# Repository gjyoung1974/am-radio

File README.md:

# AM Broadcast Receiver: 6-transistor superhet KiCad

## What it is

A classic 1960's style 455 kHz superheterodyne AM receiver, 4.5 V (3×AAA), negative ground, six 2N3904 NPN transistors:

| Stage | Parts |
|---|---|
| Antenna / tuning | L1 ferrite loopstick, VC1 2-gang polyvaricon (Variable Capacitor) (140 pF antenna gang, 60 pF oscillator gang, trimmers built in) |
| Converter (mixer + local oscillator) | Q1, L2 oscillator coil (i.e. Xicon 42IF110, red), C1 emitter injection, R1/R2/R3 bias |
| IF amp 1 with AGC | T1 (42IF101 yellow) => Q2 => T2; R4/R5/C3 form the AGC network |
| IF amp 2 | T2 (42IF102 white) => Q3 => T3 |
| Detector / volume | T3 (42IF103 black) => D1 1N34A germanium diode => C7 => RV1 10k log |
| Audio driver | C8 => Q4 => T4 (Xicon 42TU013, 1k CT : 8 CT) |
| Class-B push-pull output | Q5/Q6 => T5 (Xicon 42TU200, 200 CT : 8) => J1 speaker terminals; R14/R15 set base bias |
| Power | BT1 3×AAA (Keystone 2479 board-mount holder), SW1 slide switch, C12; R16/C13 make the decoupled `V_RF` rail for the RF/IF stages 
|Detected audio is negative-side, so AGC lowers Q2's base bias on strong stations.

## Files

- `am-radio.kicad_sch` / `am-radio.kicad_pcb` / `am-radio.kicad_pro` — the project.
- `audio.kicad_sym` — custom symbols: Xicon 42IF10x IF transformer, 42IF110 oscillator coil, 42TU013 / 42TU200 audio transformers (6-pin, pin numbers match the footprint pads), 2-gang polyvaricon, ferrite rod coil, `V_RF` power symbol. Your original `IF_Transformer_AM` symbol is kept for reference.
- `audio.pretty/` — footprints: `Xicon_42IF10x` (0.4" can, 3+3 pins on 0.135" pitch, rows 0.27" apart, from Xicon datasheet XC-600131), `Polyvaricon_CBM-223P_Wired`, `Ferrite_Rod_Antenna_Coil`, plus your `Xicon_42TU200-RC` (courtyard moved from the invalid "Rescue" layer to F.CrtYd).
- `am-radio-outputs/` — schematic PDF, grouped BOM (CSV), PCB layer PDF, top/bottom renders, gerbers + Excellon drill files.
- `am-radio-backups/original-sketch/` — your original schematic and symbol library before this rework (also in the dated backup zips).
- `tools/` — the Python generators used to build the schematic (`gen_sch.py`), libraries (`gen_libs.py`), board (`build_pcb.py`) and ground pour / labels (`finish_pcb.py`). Run with the system `python3` (it has KiCad's `pcbnew` module).

## Board

110 × 83 × 1.6 mm, 2 layers, sized to the 3D-printed case in `case/case.FCStd` (rev 1.1; the 180 × 62 mm rev 1.0 board is kept in `am-radio-backups/rev1.0-180x62/`).

Case fit (all taken from the FreeCAD model):

| Item | Value |
|---|---|
| Case | 115 × 88 × 35 mm, 2 mm walls, open top; cavity 111 × 84 mm |
| Board | 110 × 83 mm, 0.5 mm clearance per side |
| Standoffs | 4, Ø6 mm, 18 mm tall on the 2 mm base; board top face at 21.6 mm |
| Mounting holes | 2.7 mm (M2.5 self-tapping into the 2.5 mm standoff holes), centres 2.3 mm in from each edge = 105.4 × 78.4 mm pattern; 6.4 mm copper-free keepouts on both sides |
| Speaker | 76 mm square, 16 mm deep, centred under the board (board x 4.5–80.5, y 3.5–79.5); only 2 mm between it and the back of the board, so nothing is mounted on the back |
| Speaker leads | 3.5 mm pass-through hole at board (107.3, 67.5) next to J1, in the 29 mm strip east of the speaker where there is 18 mm under the board |
| Height above board | 13.4 mm to the top of the case: fine for the 10 mm IF cans and TO-92s; **check** the Keystone 2479 holder (≈13 mm), the 42TU audio transformers, and plan lid holes for the VC1 and RV1 shafts and a side slot for SW1 (it sits 4 mm from the right wall) |
| Case CornerHole | the 12 × 12 mm hole in the base plate (case X 46–58, Y 20–32) is under board x 88.5–100.5, y 9.5–21.5; only top-side parts (T2, L1, C12) are above it, so nothing on the board depends on it |

Coordinates: board x = case X + 42.5, board y = 41.5 − case Y (board origin top-left, y down, as in KiCad).

Layout: ferrite rod along the top edge with the tuning cap in the top-left corner (terminals facing the rod), 3×AAA holder standing on end along the left edge, RF chain left => right across the middle (L2, Q1, T1, Q2, T2, Q3) with T3 turning down the right edge, detector and volume pot below it, driver T4 on end in the middle, push-pull pair below it, output transformer T5 bottom-right with the speaker terminal block and wire hole beside it, power switch and C12 in the top-right corner. Full GND pour on the back. Tracks 0.6 mm (0.8–1.0 mm for GND / +BATT / V_RF), 0.2 mm clearance, 0.9/0.5 mm vias, 0.5 mm hole-to-hole.

## Things to verify before ordering a PCB

- **VC1 footprint is unverified.** No reliable drawing of the CBM-223P terminal layout exists online, so the footprint is a "wired" one: 20 × 20 mm outline, three solder pads (O, G, A) along the bottom edge for short leads, and two 2.7 mm holes for M2.5 mounting screws on a guessed 15 mm spacing. Measure your part and adjust `gen_libs.py` (or edit the footprint) if you want it to drop straight in.
- **Battery holder height.** The 3×AA holder (60 × 50 × 16 mm) did not fit the case, so BT1 is now a Keystone 2479 3×AAA holder (53.6 × 38.6 mm footprint, about 13 mm tall). Confirm its height against the 13.4 mm left above the board, or use a wired 3×AAA pack fixed to the lid and solder the leads to the BT1 pads.
- **Oscillator phasing.** If the oscillator does not start, swap the L2 pin 4 / pin 6 feedback leads (the 42IF110 datasheet does not give winding order?).

## Alignment

1. Set VC1 fully closed (max capacitance). Adjust the L2 slug so the local oscillator is at about 985 kHz (receives 530 kHz). At the high end use VC1's oscillator trimmer for about 2055 kHz (1600 kHz).
2. Peak T1, T2, T3 slugs for maximum audio on a weak station (they are pre-tuned to 455 kHz and need only a touch).
3. Peak L1 by sliding the coil along the rod at the low end of the band and with VC1's antenna trimmer at the high end.
4. Expected currents: converter ≈ 0.4 mA, IF stages ≈ 0.5 mA each, driver ≈ 1.7 mA, output pair a few mA idle. Total idle ≈ 5–8 mA at 4.5 V.

## Regenerating

```
python3 tools/gen_libs.py                       # symbols + footprints
python3 tools/gen_sch.py                        # schematic
kicad-cli sch export netlist --format kicadsexpr -o am-radio.net am-radio.kicad_sch
python3 tools/build_pcb.py am-radio.net placed.kicad_pcb          # placed, unrouted board (110 x 83, case holes, wire hole)
python3 ~/src/KiCadRoutingTools/route.py placed.kicad_pcb routed.kicad_pcb \
    --track-width 0.6 --clearance 0.2 --via-size 0.9 --via-drill 0.5 \
    --power-nets GND V_RF +BATT --power-nets-widths 0.8 0.8 1.0 \
    --board-edge-clearance 0.5 --hole-to-hole-clearance 0.5
python3 tools/finish_pcb.py routed.kicad_pcb am-radio.kicad_pcb   # GND pour, standoff keepouts, stub cleanup, labels
kicad-cli pcb drc --schematic-parity --severity-all am-radio.kicad_pcb
```

---
2026 - Gordon Young WA8Q

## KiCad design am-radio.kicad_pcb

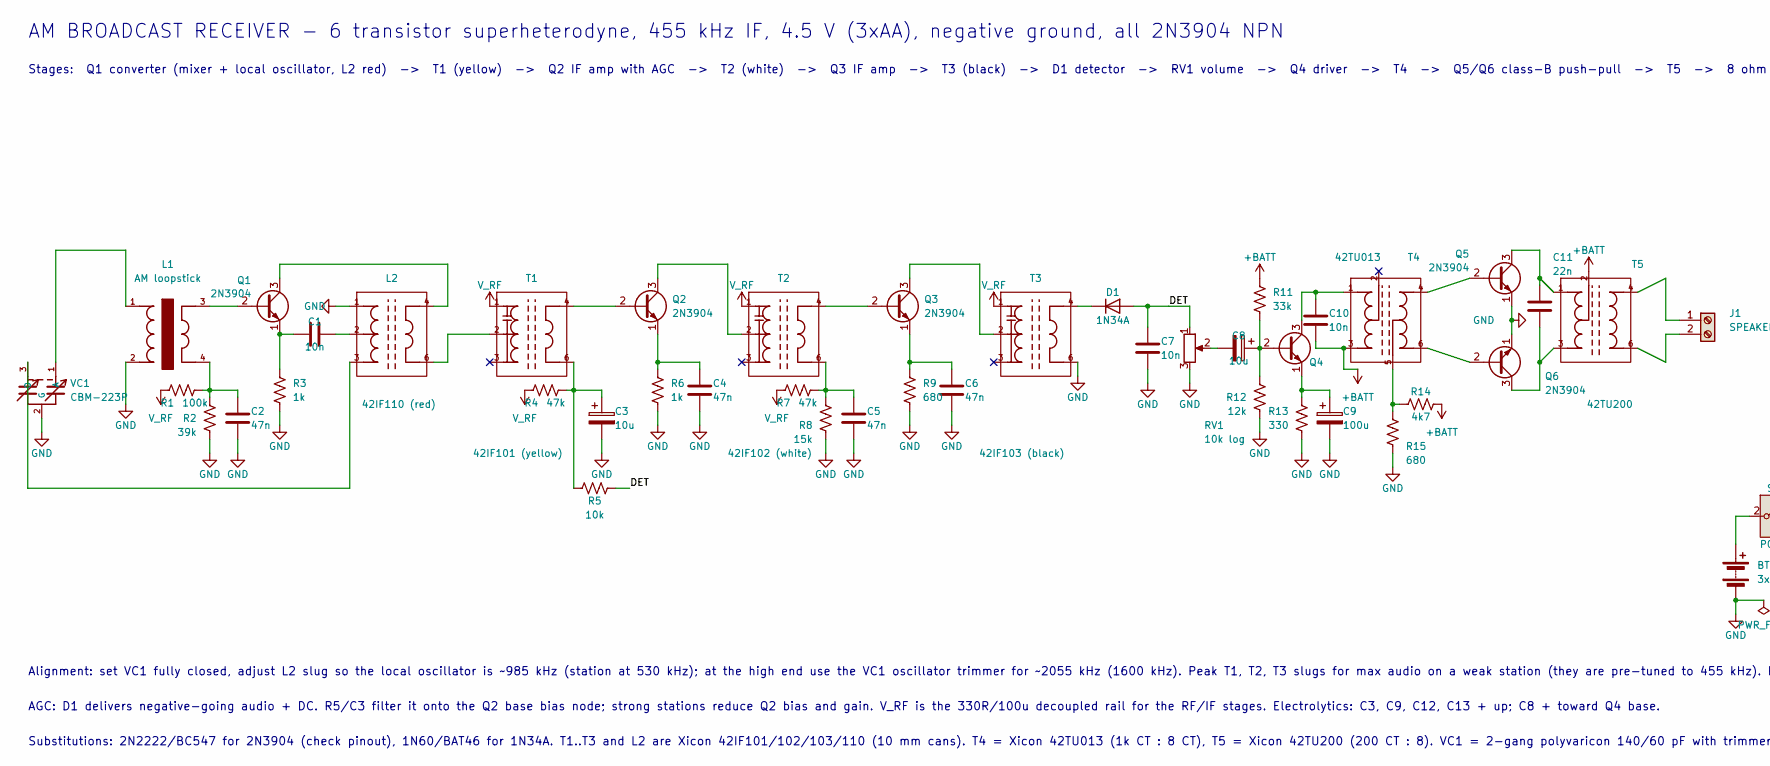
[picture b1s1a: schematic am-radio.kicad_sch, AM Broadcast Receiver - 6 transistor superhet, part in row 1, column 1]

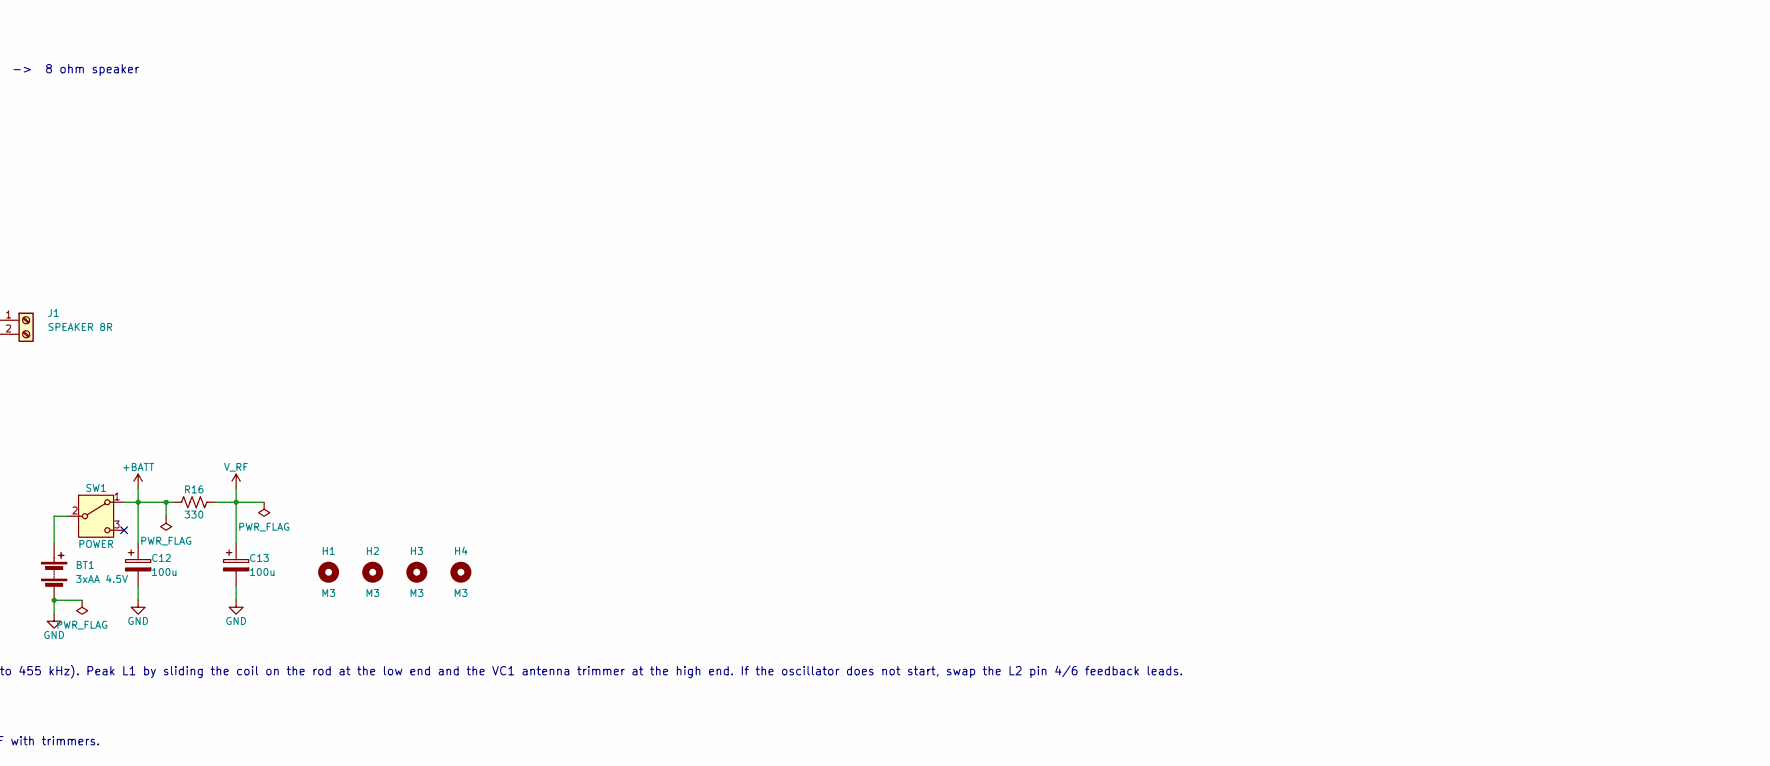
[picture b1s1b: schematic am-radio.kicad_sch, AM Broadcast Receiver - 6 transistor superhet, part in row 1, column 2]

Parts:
BT1: 3xAA 4.5V; BatteryHolder_TruPower_BH-331P_3xAA
C1, C7, C10: 10n; C_Disc_D5.0mm_W2.5mm_P5.00mm
C2, C4, C5, C6: 47n; C_Disc_D5.0mm_W2.5mm_P5.00mm
C3, C8: 10u; CP_Radial_D5.0mm_P2.00mm
C9, C12, C13: 100u; CP_Radial_D5.0mm_P2.00mm
C11: 22n; C_Disc_D5.0mm_W2.5mm_P5.00mm
D1: 1N34A; D_DO-35_SOD27_P10.16mm_Horizontal
H1, H2, H3, H4: M3; MountingHole_3.2mm_M3
J1: SPEAKER 8R; TerminalBlock_Altech_AK300-2_P5.00mm
L1: AM loopstick; Ferrite_Rod_Antenna_Coil
L2: 42IF110 (red); Xicon_42IF10x
Q1, Q2, Q3, Q4, Q5, Q6: 2N3904; TO-92
R1: 100k; R_Axial_DIN0204_L3.6mm_D1.6mm_P5.08mm_Horizontal
R2: 39k; R_Axial_DIN0204_L3.6mm_D1.6mm_P5.08mm_Horizontal
R3, R6: 1k; R_Axial_DIN0204_L3.6mm_D1.6mm_P5.08mm_Horizontal
R4, R7: 47k; R_Axial_DIN0204_L3.6mm_D1.6mm_P5.08mm_Horizontal
R5: 10k; R_Axial_DIN0204_L3.6mm_D1.6mm_P5.08mm_Horizontal
R8: 15k; R_Axial_DIN0204_L3.6mm_D1.6mm_P5.08mm_Horizontal
R9, R15: 680; R_Axial_DIN0204_L3.6mm_D1.6mm_P5.08mm_Horizontal
R11: 33k; R_Axial_DIN0204_L3.6mm_D1.6mm_P5.08mm_Horizontal
R12: 12k; R_Axial_DIN0204_L3.6mm_D1.6mm_P5.08mm_Horizontal
R13, R16: 330; R_Axial_DIN0204_L3.6mm_D1.6mm_P5.08mm_Horizontal
R14: 4k7; R_Axial_DIN0204_L3.6mm_D1.6mm_P5.08mm_Horizontal
RV1: 10k log; Potentiometer_Bourns_PTV09A-1_Single_Vertical
SW1: POWER; SW_Slide_SPDT_Straight_CK_OS102011MS2Q
T1: 42IF101 (yellow); Xicon_42IF10x
T2: 42IF102 (white); Xicon_42IF10x
T3: 42IF103 (black); Xicon_42IF10x
T4: 42TU013; Xicon_42TU200-RC
T5: 42TU200; Xicon_42TU200-RC
VC1: CBM-223P; Polyvaricon_CBM-223P_Wired

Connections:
+BATT: C10.2, C12.1, R11.1, R14.2, R16.1, SW1.1 (A), T4.3, T5.2
/DET: C7.1, D1.2 (A), R5.2, RV1.1
GND: BT1.2 (-), C2.2, C3.2, C4.2, C5.2, C6.2, C7.2, C9.2, C12.2, C13.2, L1.2, L2.1, Q5.1 (E), Q6.1 (E), R2.2, R3.2, R6.2, R8.2, R9.2, R12.2, R13.2, R15.2, RV1.3, T3.6, VC1.2 (G)
unnamed: BT1.1 (+), SW1.2 (B)
unnamed: C1.2, L2.2
unnamed: C2.1, L1.4, R1.2, R2.1
unnamed: C3.1, R4.2, R5.1, T1.6
unnamed: C5.1, R7.2, R8.1, T2.6
unnamed: C8.2, RV1.2
unnamed: D1.1 (K), T3.4
unnamed: J1.1, T5.4
unnamed: J1.2, T5.6
unnamed: L2.6, T1.2
unnamed: L1.3, Q1.2 (B)
unnamed: L2.4, Q1.3 (C)
unnamed: C1.1, Q1.1 (E), R3.1
unnamed: Q2.2 (B), T1.4
unnamed: Q2.3 (C), T2.2
unnamed: C4.1, Q2.1 (E), R6.1
unnamed: Q3.2 (B), T2.4
unnamed: Q3.3 (C), T3.2
unnamed: C6.1, Q3.1 (E), R9.1
unnamed: C8.1, Q4.2 (B), R11.2, R12.1
unnamed: C10.1, Q4.3 (C), T4.1
unnamed: C9.1, Q4.1 (E), R13.1
unnamed: Q5.2 (B), T4.4
unnamed: C11.1, Q5.3 (C), T5.1
unnamed: Q6.2 (B), T4.6
unnamed: C11.2, Q6.3 (C), T5.3
unnamed: R14.1, R15.1, T4.5
unnamed: L1.1, VC1.1 (A)
unnamed: L2.3, VC1.3 (O)
V_RF: C13.1, R1.1, R4.1, R7.1, R16.2, T1.1, T2.1, T3.1

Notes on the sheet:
AM BROADCAST RECEIVER - 6 transistor superheterodyne, 455 kHz IF, 4.5 V (3xAA), negative ground, all 2N3904 NPN
Stages: Q1 converter (mixer + local oscillator, L2 red) -> T1 (yellow) -> Q2 IF amp with AGC -> T2 (white) -> Q3 IF amp -> T3 (black) -> D1 detector -> RV1 volume -> Q4 driver -> T4 -> Q5/Q6 class-B push-pull -> T5 -> 8 ohm speaker
Alignment: set VC1 fully closed, adjust L2 slug so the local oscillator is ~985 kHz (station at 530 kHz); at the high end use the VC1 oscillator trimmer for ~2055 kHz (1600 kHz). Peak T1, T2, T3 slugs for max audio on a weak station (they are pre-tuned to 455 kHz). Peak L1 by sliding the coil on th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
AGC: D1 delivers negative-going audio + DC. R5/C3 filter it onto the Q2 base bias node; strong stations reduce Q2 bias and gain. V_RF is the 330R/100u decoupled rail for the RF/IF stages. Electrolytics: C3, C9, C12, C13 + up; C8 + toward Q4 base.
Substitutions: 2N2222/BC547 for 2N3904 (check pinout), 1N60/BAT46 for 1N34A. T1..T3 and L2 are Xicon 42IF101/102/103/110 (10 mm cans). T4 = Xicon 42TU013 (1k CT : 8 CT), T5 = Xicon 42TU200 (200 CT : 8). VC1 = 2-gang polyvaricon 140/60 pF with trimmers.

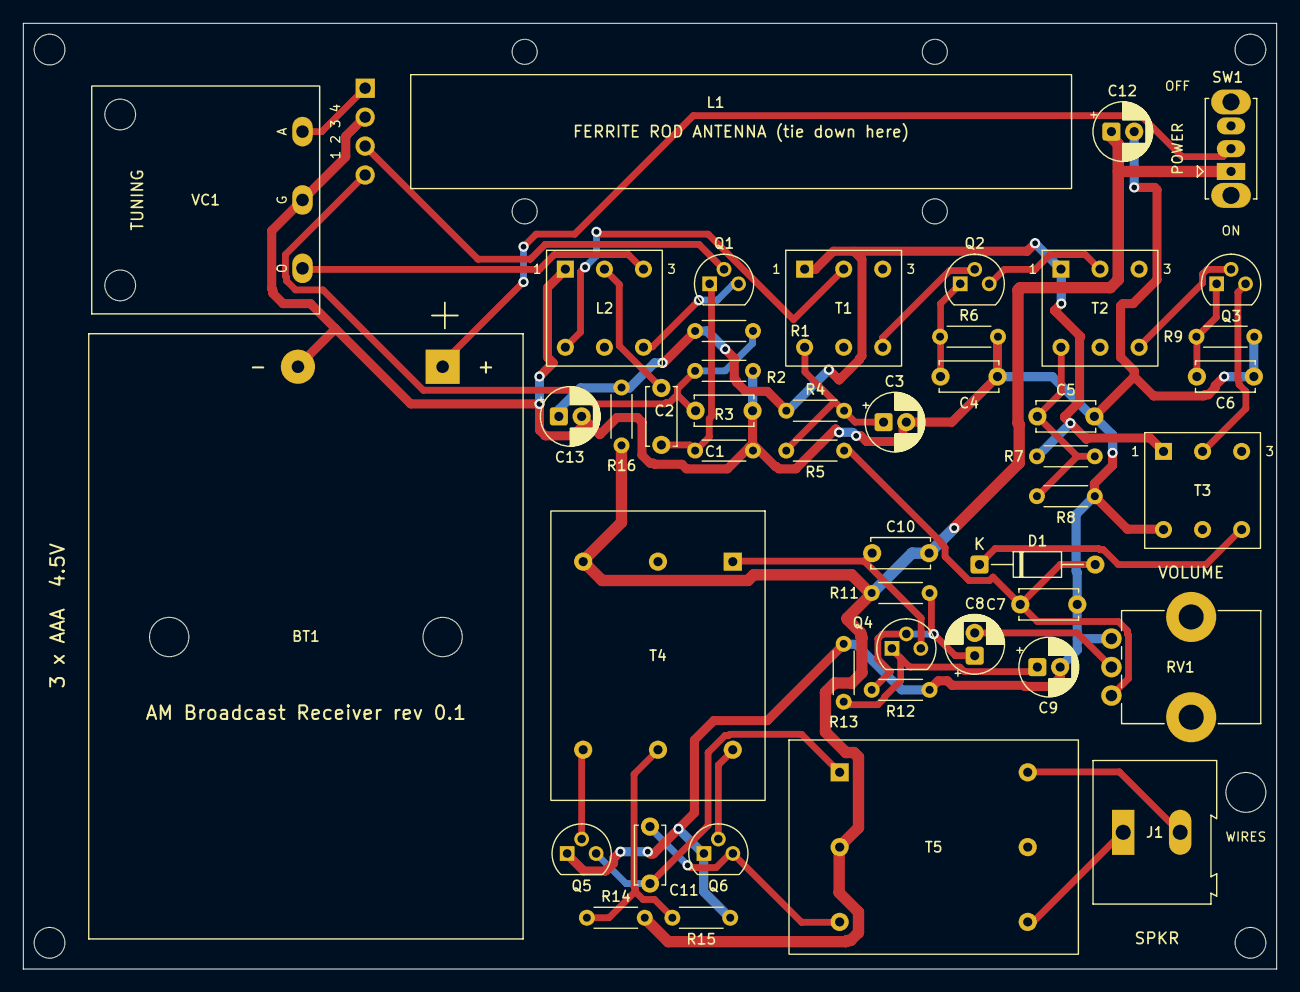
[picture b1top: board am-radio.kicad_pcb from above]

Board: 2 copper layers, 110.0 x 83.0 mm, 51 parts (0 on the bottom side), 33 nets.

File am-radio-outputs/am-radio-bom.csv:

"Ref","Value","Footprint"
"BT1","3xAAA 4.5V","Battery:BatteryHolder_Keystone_2479_3xAAA"
"C1,C7,C10","10n","Capacitor_THT:C_Disc_D5.0mm_W2.5mm_P5.00mm"
"C2,C4-C6","47n","Capacitor_THT:C_Disc_D5.0mm_W2.5mm_P5.00mm"
"C3,C8","10u","Capacitor_THT:CP_Radial_D5.0mm_P2.00mm"
"C9,C12,C13","100u","Capacitor_THT:CP_Radial_D5.0mm_P2.00mm"
"C11","22n","Capacitor_THT:C_Disc_D5.0mm_W2.5mm_P5.00mm"
"D1","1N34A","Diode_THT:D_DO-35_SOD27_P10.16mm_Horizontal"
"H1-H4","M2.5","MountingHole:MountingHole_2.7mm_M2.5"
"J1","SPEAKER 8R","TerminalBlock:TerminalBlock_Altech_AK300-2_P5.00mm"
"L1","AM loopstick","audio:Ferrite_Rod_Antenna_Coil"
"L2","42IF110 (red)","audio:Xicon_42IF10x"
"Q1-Q6","2N3904","Package_TO_SOT_THT:TO-92"
"R1","100k","Resistor_THT:R_Axial_DIN0204_L3.6mm_D1.6mm_P5.08mm_Horizontal"
"R2","39k","Resistor_THT:R_Axial_DIN0204_L3.6mm_D1.6mm_P5.08mm_Horizontal"
"R3,R6","1k","Resistor_THT:R_Axial_DIN0204_L3.6mm_D1.6mm_P5.08mm_Horizontal"
"R4,R7","47k","Resistor_THT:R_Axial_DIN0204_L3.6mm_D1.6mm_P5.08mm_Horizontal"
"R5","10k","Resistor_THT:R_Axial_DIN0204_L3.6mm_D1.6mm_P5.08mm_Horizontal"
"R8","15k","Resistor_THT:R_Axial_DIN0204_L3.6mm_D1.6mm_P5.08mm_Horizontal"
"R9,R15","680","Resistor_THT:R_Axial_DIN0204_L3.6mm_D1.6mm_P5.08mm_Horizontal"
"R11","33k","Resistor_THT:R_Axial_DIN0204_L3.6mm_D1.6mm_P5.08mm_Horizontal"
"R12","12k","Resistor_THT:R_Axial_DIN0204_L3.6mm_D1.6mm_P5.08mm_Horizontal"
"R13,R16","330","Resistor_THT:R_Axial_DIN0204_L3.6mm_D1.6mm_P5.08mm_Horizontal"
"R14","4k7","Resistor_THT:R_Axial_DIN0204_L3.6mm_D1.6mm_P5.08mm_Horizontal"
"RV1","10k log","Potentiometer_THT:Potentiometer_Bourns_PTV09A-1_Single_Vertical"
"SW1","POWER","Button_Switch_THT:SW_Slide_SPDT_Straight_CK_OS102011MS2Q"
"T1","42IF101 (yellow)","audio:Xicon_42IF10x"
"T2","42IF102 (white)","audio:Xicon_42IF10x"
"T3","42IF103 (black)","audio:Xicon_42IF10x"
"T4","42TU013","audio:Xicon_42TU200-RC"
"T5","42TU200","audio:Xicon_42TU200-RC"
"VC1","CBM-223P","audio:Polyvaricon_CBM-223P_Wired"
